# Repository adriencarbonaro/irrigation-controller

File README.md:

# irrigation_controller

## Overview
This controller is used to remotely control a drip irrigation system.  

It controls up to 3 irrigation zones and, optionally, a submersible pump.

Home Assistant controls the watering sequences:
- activation of the irrigation controller, programmable start time of the irrigation sequence
- behavior of each zone (availability and watering duration)  

## Features
### On the irrigation controller
- water inlet: one 3/4" connection, on the right side
- water outlets: 1, 2, or 3 × 3/4" connections, facing downward
- for each outlet:
    - a manual control button (all 3 valves can be opened at the same time)
    - a LED that lights up when the valve is open
- a safety timeout turns off the valves after _EV_timeout_ minutes of activation
- the status LED blinks when WiFi is connected
- the controller is powered from 230 V AC

### In Home Assistant
A button makes the controller active (watering according to the zone parameters) or inactive (no watering).

Start time: HH:MM [0:00 to 23:59], when the watering sequence shall start.

The behavior of each zone is defined in Home Assistant with the following parameters:
- availability: true if the zone is used, false if it is not used
- days of week: frequency of watering _(to be added)_
- duration: watering duration in minutes [1 to 15]
- frequency: 1 cycle (every 24h), 2 cycles (every 12h), 3 cycles (every 6h) _(to be added)_
- a button to manually operate the zone (immediate start on the 1st push, immediate stop on the 2nd push)  
- rain sensor: disables the watering sequence while it is raining _(to be added)_

Sequence definition: at the start time, zone 1 is operated for the given duration if it is activated, then zone 2, then zone 3.

## Hardware

### 🙌 Sponsor
Huge thanks to PCBWay for sponsoring the PCB manufacturing for this project. Their support, help and advices helped make this project physically real.

If you're looking for high-quality PCB fabrication or assembly services, check them out:

👉 https://www.pcbway.com

### Electronics

Schematic & PCB designed using KiCad 9

- Microcontroller: Seeed Studio XIAO ESP32-C3
- 12 V solenoid valve control: power MOSFET IRFZ24N (55 V, 17 A)
- Submersible pump control: 230 V Triac BT136-600

**Final design**
PCB dimensions 148 × 61 mm, 4 mounting holes (141.4 × 45 mm)

**Various configurations are available**
a) 2 valves + 1 pump  

The D5 LED (= TRIAC is active) is optional.

b) 3 valves, no pump  
Yet to come

### Hydraulic
- Inlet: 3/4" (20/27) for an automatic garden connection
- Outlet: 3/4" (20/27) for an automatic garden connection
- solenoid valves: 12 V DC, NC, 0.02 - 0.8 MPa, 1/2" (15/21) solenoid valve, from a washing machine
- 14 mm copper pipes

## Firmware
- The ESP32 module manages
    - the GPIOs
    - a script to drive the solenoid valves and the submersible pump
    - a safety timeout to stop watering in case HA is disconnected during a watering sequence
- HA manages the irrigation sequences and the manual control through a card in the "garden" dashboard

### ESPHome firmware
binary sensor:  
- SW3, SW2, SW1 (must be high at boot): manual command on the device
- ev1_active, ev2_active: provide HA with the actual status of the solenoid valves

switch: ON/OFF command
- EV1, EV2, EV3: commands for the 3 solenoid valves
- pump control: submersible pump command

output:
- status LED (HIGH side command)

sensor:
- WiFi RSSI in dBm

button:  
- 3 virtual buttons to manually control EV1, EV2 and EV3 in HA

wifi:
- automatically connects to any of the 3 WiFi routers in the home

light:
(The binary light platform creates a simple ON/OFF-only light from a binary output component.)
- **led_status**: blinks the status LED according to LED_ON (100 ms) and LED_OFF (4900 ms)  

script:
- **toggle_EV1, toggle_EV2, toggle_EV3**: turn the given solenoid valve on and off; turn on the submersible pump when at least one valve is on, and turn it off when all valves are off; launch the safety timeout  
- **valves_safety_timeout**: turns off every command after EV_timeout (typically 30 min)  

### Home Assistant configuration

All the elements linked to the irrigation controller are found under the label "irrigation".

#### Device
- add "irrigation_ctl1" under Settings → Devices & Services → ESPHome

#### Entities
The actionable entities are:
- EVi command: executes the script `toggle_EVi`
- pump: `switch_toggle` pump
- EVi: `switch_toggle` solenoid valve i

#### Helpers
- common to all zones:
  - `irrigation_auto`: enables the automatic watering program
  - `irrigation_heure_debut` (watering start time): the time at which watering starts
- for each zone (i = 1, 2 or 3):
  - `irrigation_active_zonei`: enables the watering program on zone i
  - `irrigation_duree_zonei` (watering duration zonei): the watering duration of zone i

#### Script
- `lancer_goutteAgoutte_1` (run drip irrigation): executes `commande_EVi` if `irrigation_active_zonei` is true, for the duration `irrigation_duree_zonei`

#### Automation
- `Démarrage irrigation` (Start irrigation): at `irrigation_heure_debut`, executes the script `lancer_goutteAgoutte_1` if `irrigation_auto` is set to true

#### Dashboard
a) 2 valves version, french language
- Mode Auto ('Auto mode'): makes the controller active (watering according to the zone parameters) or inactive (no watering)
- Heure Début ('Start time'): the start time of the watering sequence
- Zone 1, Zone 2: a single click manually starts the watering of the selected zone. A second click stops the watering. While watering is on, the icon turns red.
- Activé/desactivé ('Enabled/Disabled'): if enabled, the zone is included in the watering sequence
- Duration: automatic watering duration, from 1 min to 15 min

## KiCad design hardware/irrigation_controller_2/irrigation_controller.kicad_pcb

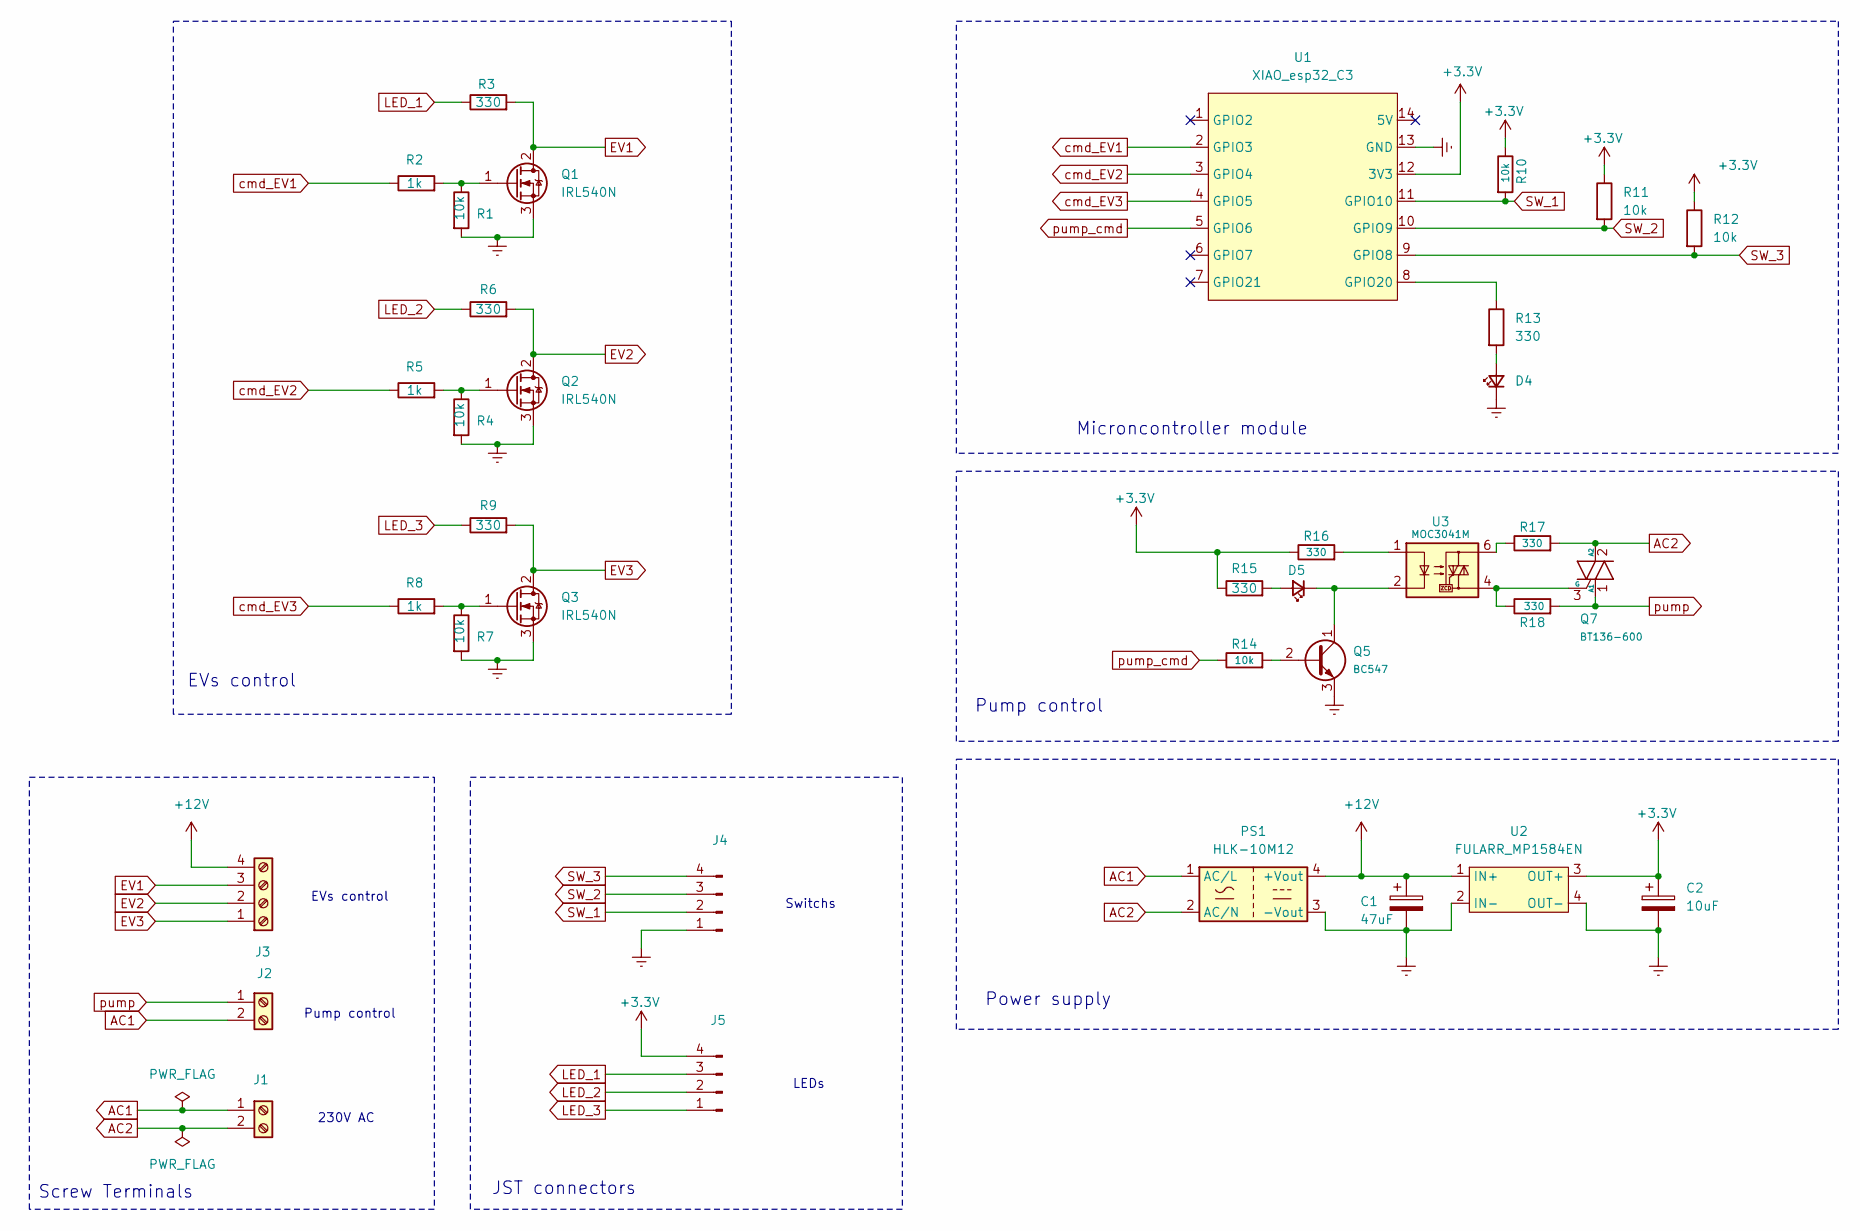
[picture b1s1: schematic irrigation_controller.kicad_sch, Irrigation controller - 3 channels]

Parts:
C1: 47uF; CP_Radial_D6.3mm_P2.50mm
C2: 10uF; CP_Radial_D5.0mm_P2.50mm
D4: LED_Small; LED_D5.0mm
D5: LED_Small; LED_0805_2012Metric_Pad1.15x1.40mm_HandSolder
J1, J2: Screw_Terminal_01x02; TerminalBlock_bornier-2_P5.08mm
J3: Screw_Terminal_01x04; TerminalBlock_bornier-4_P5.08mm
J4, J5: Conn_01x04_Pin; JST_XH_B4B-XH-A_1x04_P2.50mm_Vertical
PS1: HLK-10M12; Converter_ACDC_Hi-Link_HLK-10Mxx
Q1, Q2, Q3: IRL540N; TO-220-3_Vertical
Q5: BC547; TO-92_Inline
Q7: BT136-600; TO-252-3_TabPin2
R1, R4, R7, R10, R11, R12, R14: 10k; R_1206_3216Metric_Pad1.30x1.75mm_HandSolder
R2, R5, R8: 1k; R_1206_3216Metric_Pad1.30x1.75mm_HandSolder
R3, R6, R9, R13, R15, R16, R17, R18: 330; R_1206_3216Metric_Pad1.30x1.75mm_HandSolder
U1: XIAO_esp32_C3; XIAO_ESP32_C3
U2: FULARR_MP1584EN
U3: MOC3041M; DIP-6_W7.62mm

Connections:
+3.3V: C2.1, J5.4, R10.1, R11.1, R12.1, R15.1, R16.1, U1.12 (3V3), U2.3 (OUT+)
+12V: C1.1, J3.4, PS1.4 (+Vout), U2.1 (IN+)
AC1: J1.1, J2.2, PS1.1 (AC/L)
AC2: J1.2, PS1.2 (AC/N), Q7.2 (A2), R17.2
EV1: J3.3, Q1.2 (D), R3.2
EV2: J3.2, Q2.2 (D), R6.2
EV3: J3.1, Q3.2 (D), R9.2
GND: C1.2, C2.2, D4.1 (K), J4.1, PS1.3 (-Vout), Q1.3 (S), Q2.3 (S), Q3.3 (S), Q5.3 (E), R1.2, R4.2, R7.2, U1.13 (GND), U2.2 (IN-), U2.4 (OUT-)
LED_1: J5.3, R3.1
LED_2: J5.2, R6.1
LED_3: J5.1, R9.1
unnamed: D4.2 (A), R13.2
unnamed: D5.2 (A), R15.2
unnamed: D5.1 (K), Q5.1 (C), U3.2
unnamed: Q1.1 (G), R1.1, R2.2
unnamed: Q2.1 (G), R4.1, R5.2
unnamed: Q3.1 (G), R7.1, R8.2
unnamed: Q5.2 (B), R14.2
unnamed: Q7.3 (G), R18.1, U3.4
unnamed: R16.2, U3.1
unnamed: R17.1, U3.6
unnamed: R13.1, U1.8 (GPIO20)
SW_1: J4.2, R10.2, U1.11 (GPIO10)
SW_2: J4.3, R11.2, U1.10 (GPIO9)
SW_3: J4.4, R12.2, U1.9 (GPIO8)
cmd_EV1: R2.1, U1.2 (GPIO3)
cmd_EV2: R5.1, U1.3 (GPIO4)
cmd_EV3: R8.1, U1.4 (GPIO5)
pump: J2.1, Q7.1 (A1), R18.2
pump_cmd: R14.1, U1.5 (GPIO6)

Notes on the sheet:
LEDs
JST connectors
Microncontroller module
EVs control
Pump control
Power supply
Screw Terminals
Switchs
230V AC

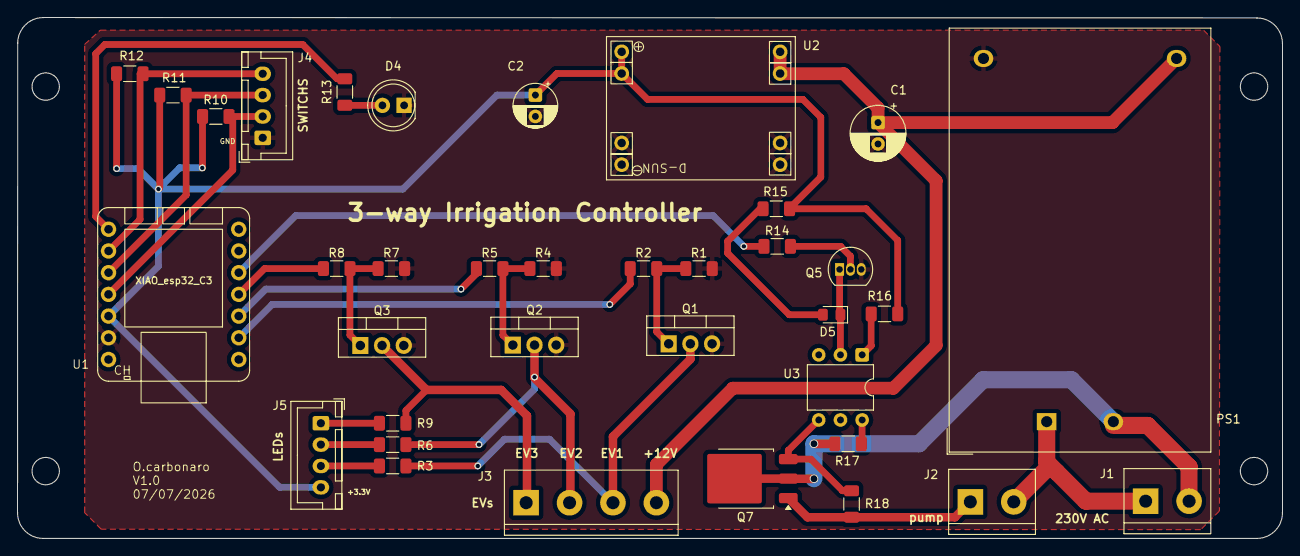
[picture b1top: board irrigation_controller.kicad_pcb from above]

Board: 2 copper layers, 148.0 x 61.0 mm, 36 parts (0 on the bottom side), 30 nets.

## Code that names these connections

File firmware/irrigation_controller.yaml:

# Board: Generic ESP32-C3 Board (Generic)
# Definition: definitions/boards/generic-esp32c3/manifest.yaml
# V0.9.0 : prototype version

# module specific parameters
substitutions:
  nom_appareil: irrigation-ctrl1
  nom_friendly: irrigation_ctrl1
  nom_projet: OC.irrigation_controller_V1
  version: "0.9.0"
  LED_ON: "100"
  LED_OFF: "5000"
  EV_timeout: "30"

globals:
  - type: bool
    id: ev1_active
    initial_value: "false"
  - type: bool
    id: ev2_active
    initial_value: "false"
    
esphome:
  name: ${nom_appareil}
  friendly_name: ${nom_friendly}
  project:
    name: ${nom_projet}
    version: ${version}
  on_loop:
    - then:
        - script.execute: blink_LED
esp32:
  variant: ESP32C3
  framework:
    type: esp-idf

logger:

api:
  encryption:
    key: "pxbvuG+20dlxeLNGQ+HZN8x13qUB9Y79AQnYE4bcN6g="

ota:
  - platform: esphome

wifi:
  ap:
    ssid: irrigation_cont Fallback Hotspot
    password: "si6GjbceibFG"

  networks:
    - id: maison
      ssid: !secret wifi_maison_ssid
      password: !secret wifi_password
    - id: poules
      ssid: !secret wifi_poules_ssid
      password: !secret wifi_password
    - id: atelier
      ssid: !secret wifi_atelier_ssid
      password: !secret wifi_password
captive_portal:

sensor:
# mesure wifi RSSI in dBm
  - platform: wifi_signal
    name: "RSSI WiFi"
    id: wifi_signal_db
    update_interval: 60s
    entity_category: diagnostic
    icon: "mdi:signal"
    
switch:
# irrigation solenoid valve 1 control
  - platform: gpio
    name: valve1
    pin: GPIO3
    id: switch_valve1
# irrigation solenoid valve 2 control
  - platform: gpio
    name: valve2
    pin: GPIO4
    id: switch_valve2
  # pump control
  - platform: gpio
    name: pump
    pin: GPIO5
    id: switch_pump
  # Status LED
  - platform: gpio
    name: LED
    pin: GPIO20
    id: switch_LED
    
binary_sensor:
  # EV1 manual control button
  - platform: gpio
    name: bouton1
    pin:  GPIO8
    id: button_EV1
    filters:
      - invert:
    on_click:
      - then:
          - script.execute: toggle_EV1
  # EV2 manual control button
  - platform: gpio
    name: bouton2
    pin: GPIO9
    id: button_EV2
    filters:
      - invert:
    on_click:
      - then:
          - script.execute: toggle_EV2

button:
  # virtual button ton manually control EV1 in HA
  - platform: template
    name: Commande EV1
    id: button_control_EV1
    on_press:
      - then:
          - script.execute: toggle_EV1
  # virtual button ton manually control EV2 in HA            
  - platform: template
    name: Commande EV2
    id: button_control_EV2
    on_press:
      - then:
          - script.execute: toggle_EV2  
            
script:
  # Blink LED 
  - id: blink_LED
    mode: single
    then:
      - switch.turn_on: switch_LED
      - delay:
          milliseconds: ${LED_ON}
      - switch.turn_off: switch_LED
      - delay:
          milliseconds: ${LED_OFF}
          
    # EV1 + pump control 
    # - toggles EV1
    # - if at least one EV is active, turn on pump and launch securityt timeout
  - id: toggle_EV1
    mode: single
    then:
      - lambda: |
          id(ev1_active) = !id(ev1_active);
      - switch.toggle: switch_valve1
      - if:
          condition:
            lambda: |
              return id(ev1_active)|id(ev2_active);
          then:
            - switch.turn_on: switch_pump
            - script.execute: valves_security_timeout
          else:
            - switch.turn_off: switch_pump
            - script.stop: valves_security_timeout
              
    # EV2 + pump control 
    # - toggles EV2
    # - if at least one EV is active, turn on pump and launch securityt timeout
  - id: toggle_EV2
    mode: single
    then:
      - lambda: |
          id(ev2_active) = !id(ev2_active);
      - switch.toggle: switch_valve2
      - if:
          condition:
            lambda: |
              return id(ev1_active)|id(ev2_active);
          then:
            - switch.turn_on: switch_pump
            - script.execute: valves_security_timeout
          else:
            - switch.turn_off: switch_pump
            - script.stop: valves_security_timeout

    # security timeout: turns off every command after EV_timeout
  - id: valves_security_timeout
    mode : restart
    then:
      - delay:
          minutes: ${EV_timeout}
      - switch.turn_off: switch_valve1
      - switch.turn_off: switch_valve2
      - switch.turn_off: switch_pump
